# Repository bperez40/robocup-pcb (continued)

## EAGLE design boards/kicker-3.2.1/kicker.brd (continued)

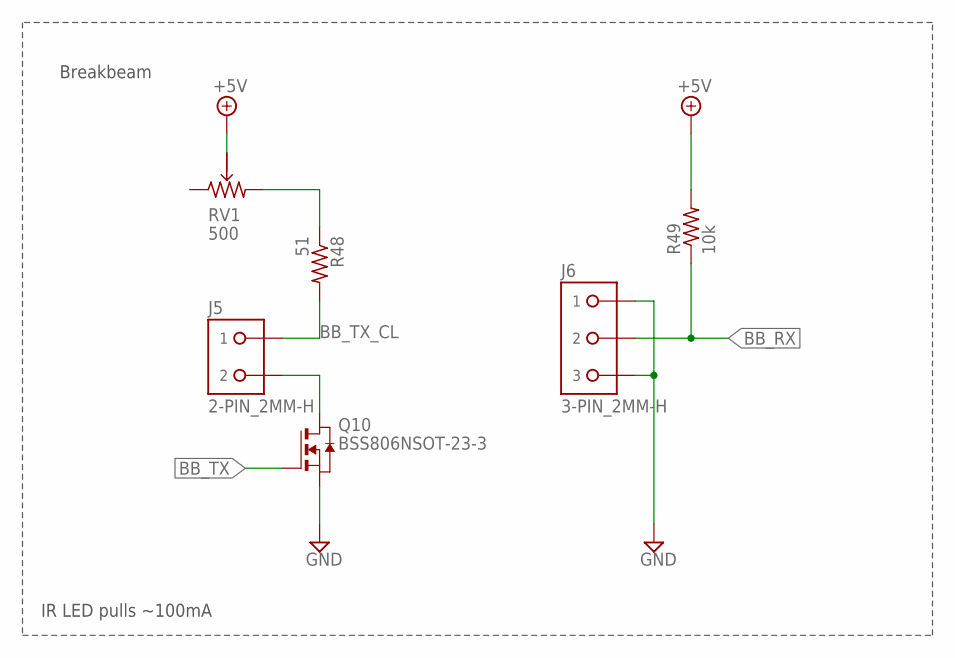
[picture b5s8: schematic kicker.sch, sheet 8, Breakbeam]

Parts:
J5: 2-PIN_2MM-H; 2MM-2-H
J6: 3-PIN_2MM-H; 2MM-3-H
Q10: BSS806NSOT-23-3; SOT95P240X110-3
R48: 51; R0603
R49: 10k; R0603
RV1: 500; PVG3G

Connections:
+5V: R49.2, RV1.P$2 (PIN2); also elsewhere on the board
BB_RX: J6.2, R49.1; also elsewhere on the board
BB_TX: Q10.1 (G); also elsewhere on the board
BB_TX_CL: J5.1, R48.2
GND: J6.1, J6.3, Q10.2 (S); also elsewhere on the board
unnamed: R48.1, RV1.P$3 (PIN3)
unnamed: J5.2, Q10.3 (D)

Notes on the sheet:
Breakbeam
IR LED pulls ~100mA

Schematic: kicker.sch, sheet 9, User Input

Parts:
J7: !BTN_KCK_PRE_EXT; 1X2
J8: !BTN_CHP_PRE_EXT; 1X2
J9: !BTN_CHG_PRE_EXT; 1X2
R50, R51, R52, R53: 10k; R0603
S1: CSS-121XB
S2, S3, S4: HDP001R

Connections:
!BTN_CHG: J9.1, R53.1, S4.C (A2); also elsewhere on the board
!BTN_CHP: J8.1, R51.1, S2.C (A2); also elsewhere on the board
!BTN_KCK: J7.1, R52.1, S3.C (A2); also elsewhere on the board
+5V: R51.2, R52.2, R53.2, S1.1 (A); also elsewhere on the board
GND: J7.2, J8.2, J9.2, S1.2 (B), S1.LEG1, S1.LEG4 (LEG2), S2.B (B1), S3.B (B1), S4.B (B1); also elsewhere on the board
MODE_SELECT: R50.2; also elsewhere on the board
unnamed: R50.1, S1.3 (COMMON)

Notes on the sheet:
Debug Mode Select
Chip/Kick Switch
Solder-in Debug Lines

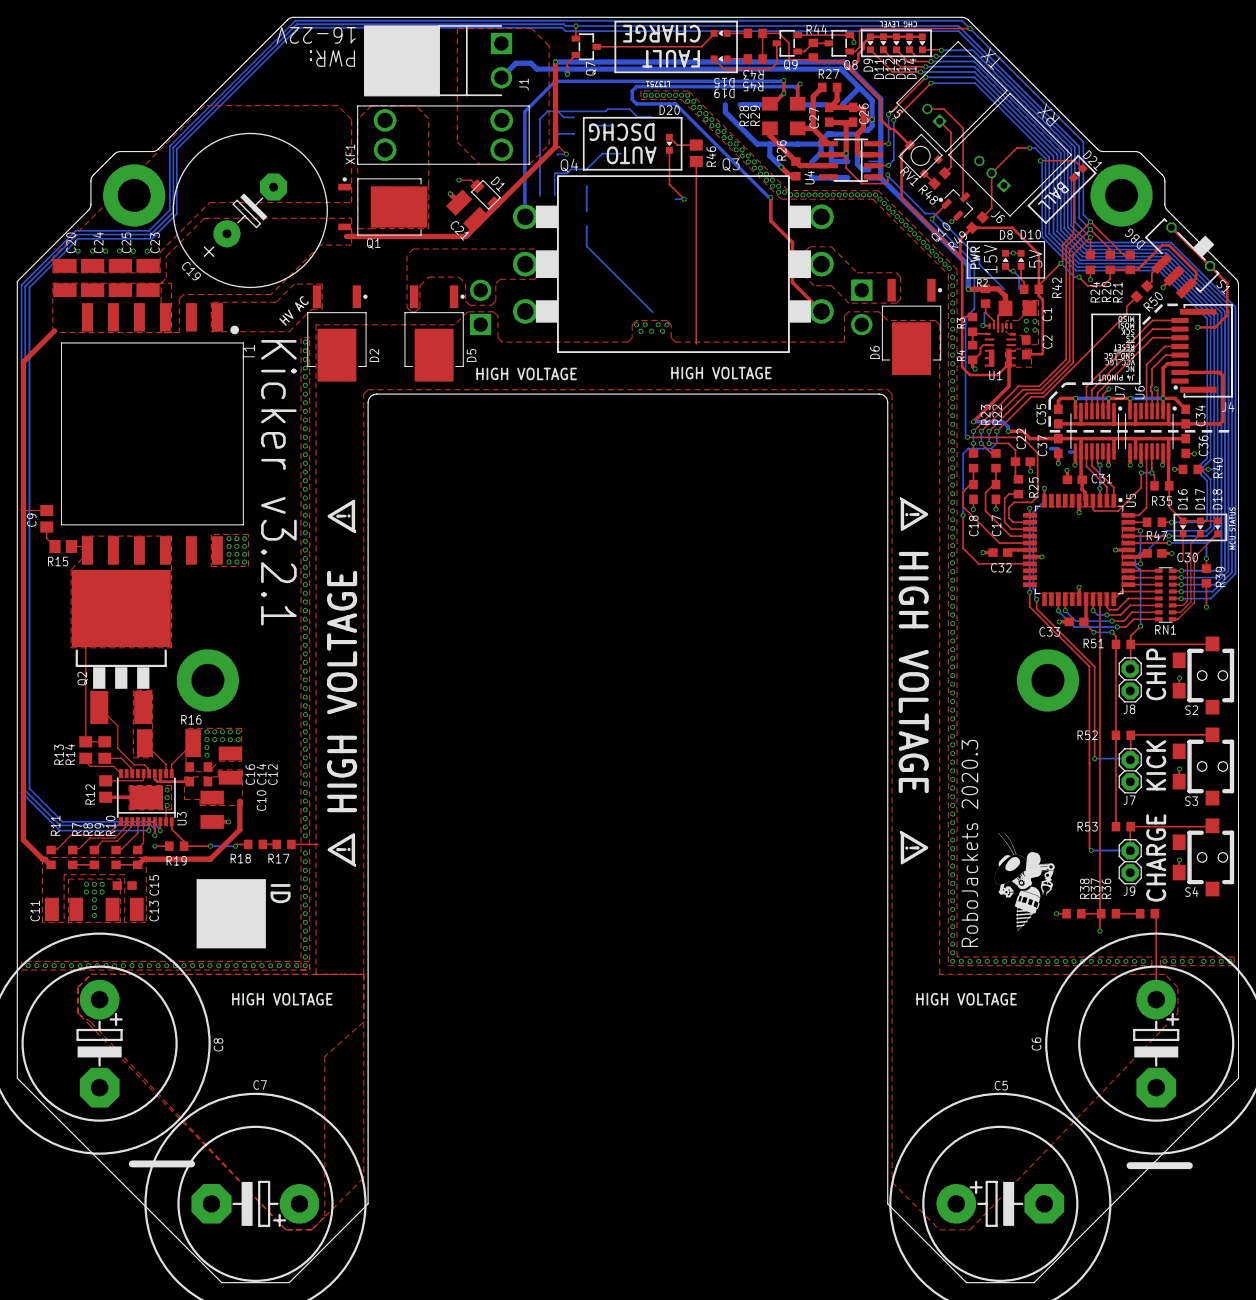
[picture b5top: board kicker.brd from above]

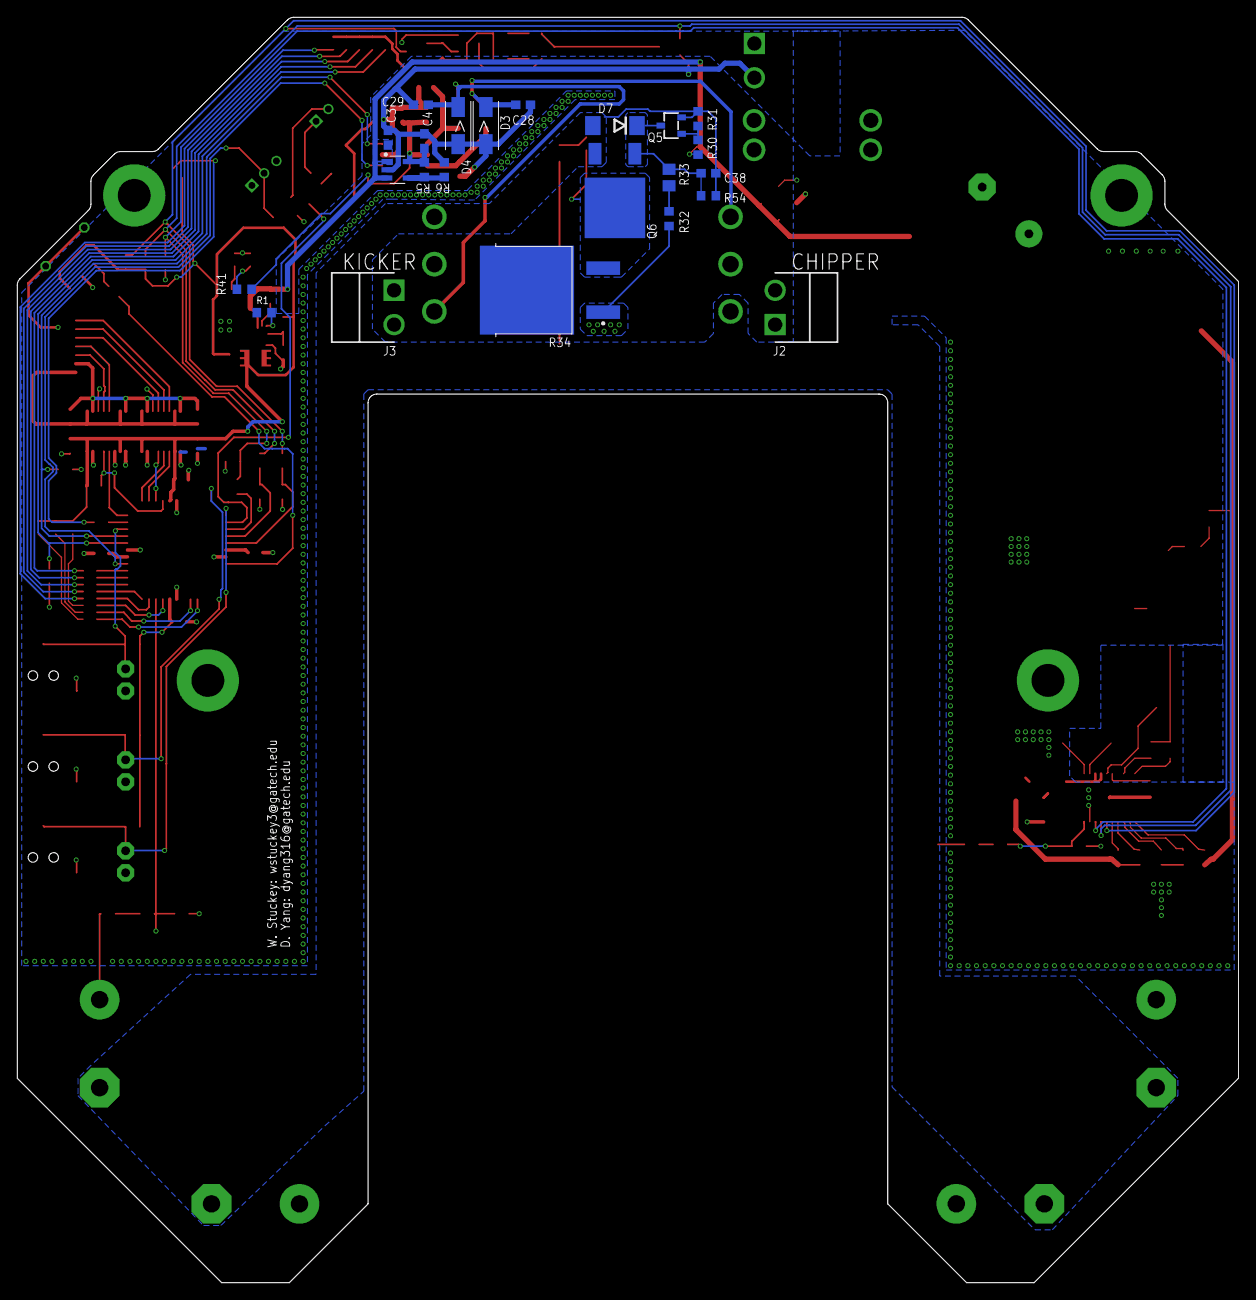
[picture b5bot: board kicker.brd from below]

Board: 2 copper layers, 141.0 x 146.1 mm, 152 parts (23 on the bottom side), 94 nets.

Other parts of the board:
U$1, U$2, U$3, U$4: WARNING2
U$5: ROBOBUZZ_0.6X

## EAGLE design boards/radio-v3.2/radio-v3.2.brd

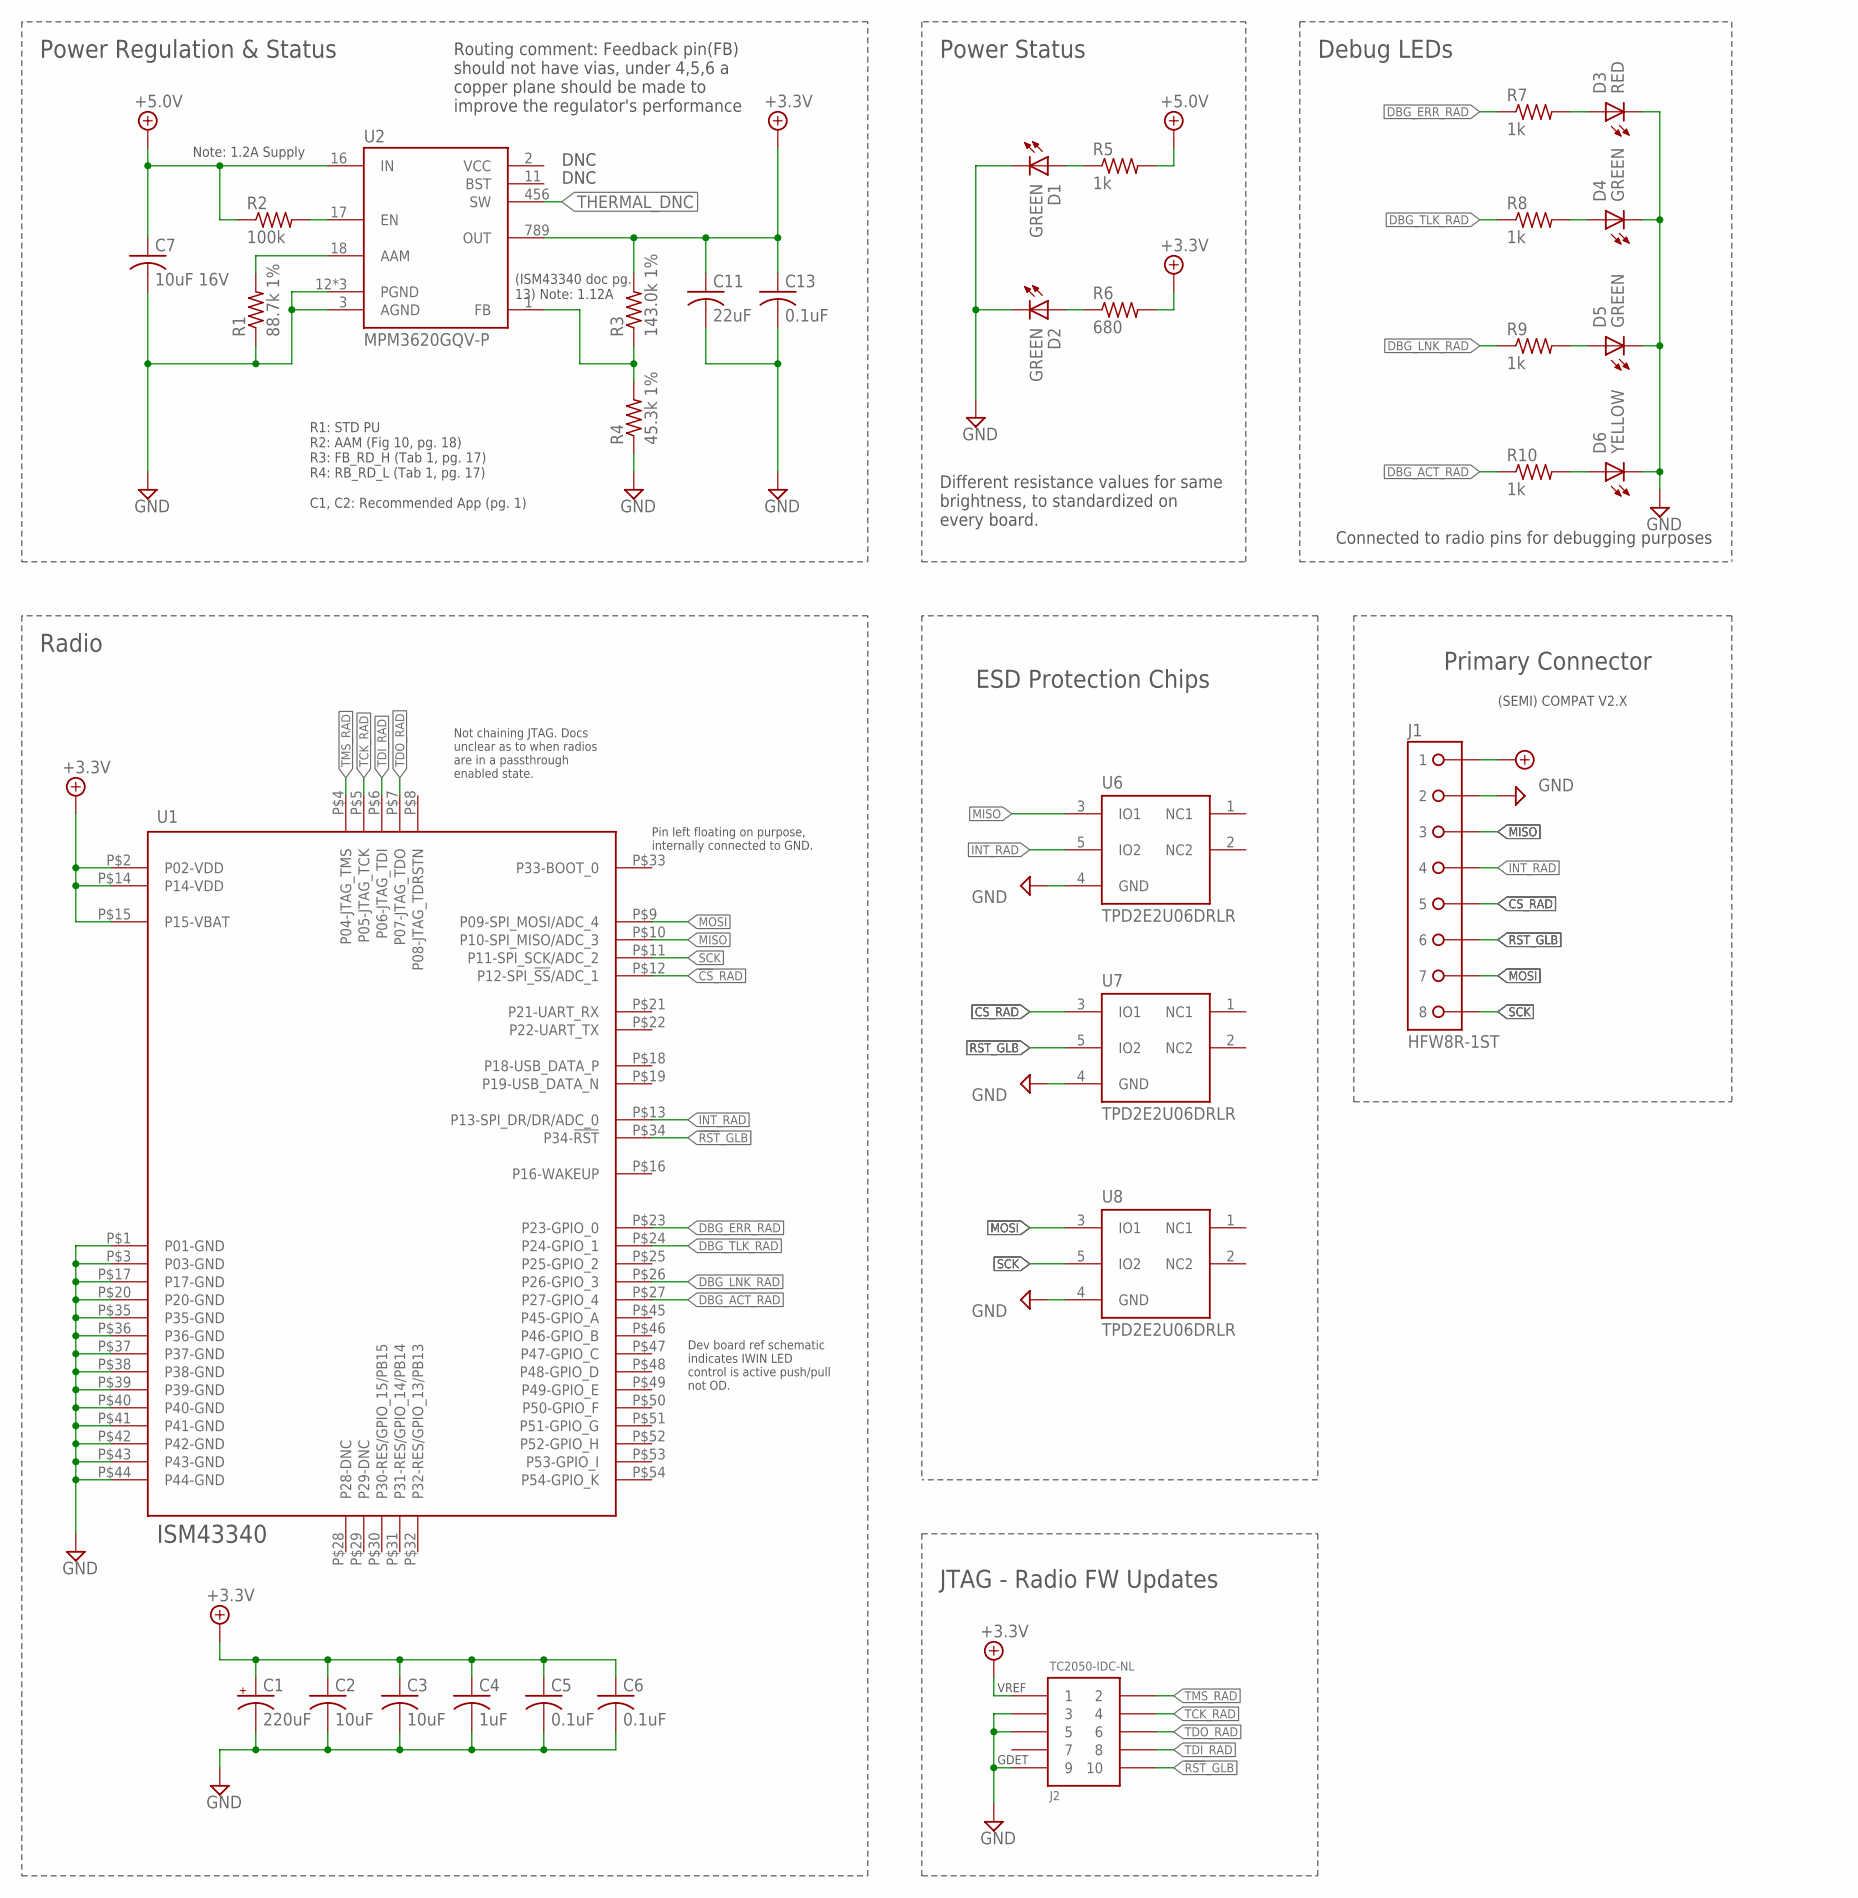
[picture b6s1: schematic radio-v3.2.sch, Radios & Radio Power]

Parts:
C1: 220uF; ECA-0JM221-HGT_HORIZ
C2, C3: 10uF; C0805
C4: 1uF; C0603
C5, C6, C13: 0.1uF; C0603
C7: 10uF 16V; C1210
C11: 22uF; C1210
D1, D2, D4, D5: GREEN; CHIP-LED0603
D3: RED; CHIP-LED0603
D6: YELLOW; CHIP-LED0603
J1: HFW8R-1ST
J2: TC2050-IDC-NL
R1: 88.7k 1%; R0603
R2: 100k; R0603
R3: 143.0k 1%; R0603
R4: 45.3k 1%; R0603
R5, R7, R8, R9, R10: 1k; R0603
R6: 680; R0603
U1: ISM43340
U2: MPM3620GQV-P
U6, U7, U8: TPD2E2U06DRLR; SOT-553

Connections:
3V3_PWR_IND: D2.A, R6.1
5V_PWR_IND: D1.A, R5.1
!CS!_RAD: J1.5, U1.P$12 (P12-SPI_!SS!/ADC_1), U7.3 (IO1)
!RST!_GLB: J1.6, J2.P$10 (10), U1.P$34 (P34-!RST!), U7.5 (IO2)
+3.3V: C1.P$1 (+), C2.1, C3.1, C4.1, C5.1, C6.1, C11.1, C13.1, J2.P$1 (1), R3.2, R6.2, U1.P$2 (P02-VDD), U1.P$14 (P14-VDD), U1.P$15 (P15-VBAT), U2.789 (OUT)
+5.0V: C7.1, J1.1, R2.1, R5.2, U2.16 (IN)
AAM: R1.2, U2.18 (AAM)
DBG_ACT_RAD: R10.1, U1.P$27 (P27-GPIO_4)
DBG_ERR: D3.A, R7.2
DBG_ERR_RAD: R7.1, U1.P$23 (P23-GPIO_0)
DBG_LNK_RAD: R9.1, U1.P$26 (P26-GPIO_3)
DBG_TLK_RAD: R8.1, U1.P$24 (P24-GPIO_1)
DGB_ACT: D6.A, R10.2
DGB_LNK: D5.A, R9.2
EN: R2.2, U2.17 (EN)
FB: R3.1, R4.2, U2.1 (FB)
GND: C1.P$2 (-), C2.2, C3.2, C4.2, C5.2, C6.2, C7.2, C11.2, C13.2, D1.C (K), D2.C (K), D3.C (K), D4.C (K), D5.C (K), D6.C (K), J1.2, J2.P$3 (3), J2.P$5 (5), J2.P$9 (9), R1.1, R4.1, U1.P$1 (P01-GND), U1.P$3 (P03-GND), U1.P$17 (P17-GND), U1.P$20 (P20-GND), U1.P$35 (P35-GND), U1.P$36 (P36-GND), U1.P$37 (P37-GND), U1.P$38 (P38-GND), U1.P$39 (P39-GND), U1.P$40 (P40-GND), U1.P$41 (P41-GND), U1.P$42 (P42-GND), U1.P$43 (P43-GND), U1.P$44 (P44-GND), U2.3 (AGND), U2.12 (PGND), U2.13 (PGND), U2.14 (PGND), U6.4 (GND), U7.4 (GND), U8.4 (GND)
INT_RAD: J1.4, U1.P$13 (P13-SPI_DR/DR/ADC_0), U6.5 (IO2)
MISO: J1.3, U1.P$10 (P10-SPI_MISO/ADC_3), U6.3 (IO1)
MOSI: J1.7, U1.P$9 (P09-SPI_MOSI/ADC_4), U8.3 (IO1)
SCK: J1.8, U1.P$11 (P11-SPI_SCK/ADC_2), U8.5 (IO2)
TCK_RAD: J2.P$4 (4), U1.P$5 (P05-JTAG_TCK)
TDI_RAD: J2.P$8 (8), U1.P$6 (P06-JTAG_TDI)
TDO_RAD: J2.P$6 (6), U1.P$7 (P07-JTAG_TDO)
THERMAL_DNC: U2.456 (SW)
TLK: D4.A, R8.2
TMS_RAD: J2.P$2 (2), U1.P$4 (P04-JTAG_TMS)

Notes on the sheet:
DNC
Primary Connector
Power Regulation & Status
Power Status
Note: 1.2A Supply
(ISM43340 doc pg. 13) Note: 1.12A
R1: STD PU R2: AAM (Fig 10, pg. 18) R3: FB_RD_H (Tab 1, pg. 17) R4: RB_RD_L (Tab 1, pg. 17) C1, C2: Recommended App (pg. 1)
Radio
Debug LEDs
VREF
GDET
JTAG - Radio FW Updates
Dev board ref schematic indicates IWIN LED control is active push/pull not OD.
Not chaining JTAG. Docs unclear as to when radios are in a passthrough enabled state.
(SEMI) COMPAT V2.X
ESD Protection Chips
Pin left floating on purpose, internally connected to GND.
Routing comment: Feedback pin(FB) should not have vias, under 4,5,6 a copper plane should be made to improve the regulator's performance
Connected to radio pins for debugging purposes
Different resistance values for same brightness, to standardized on every board.

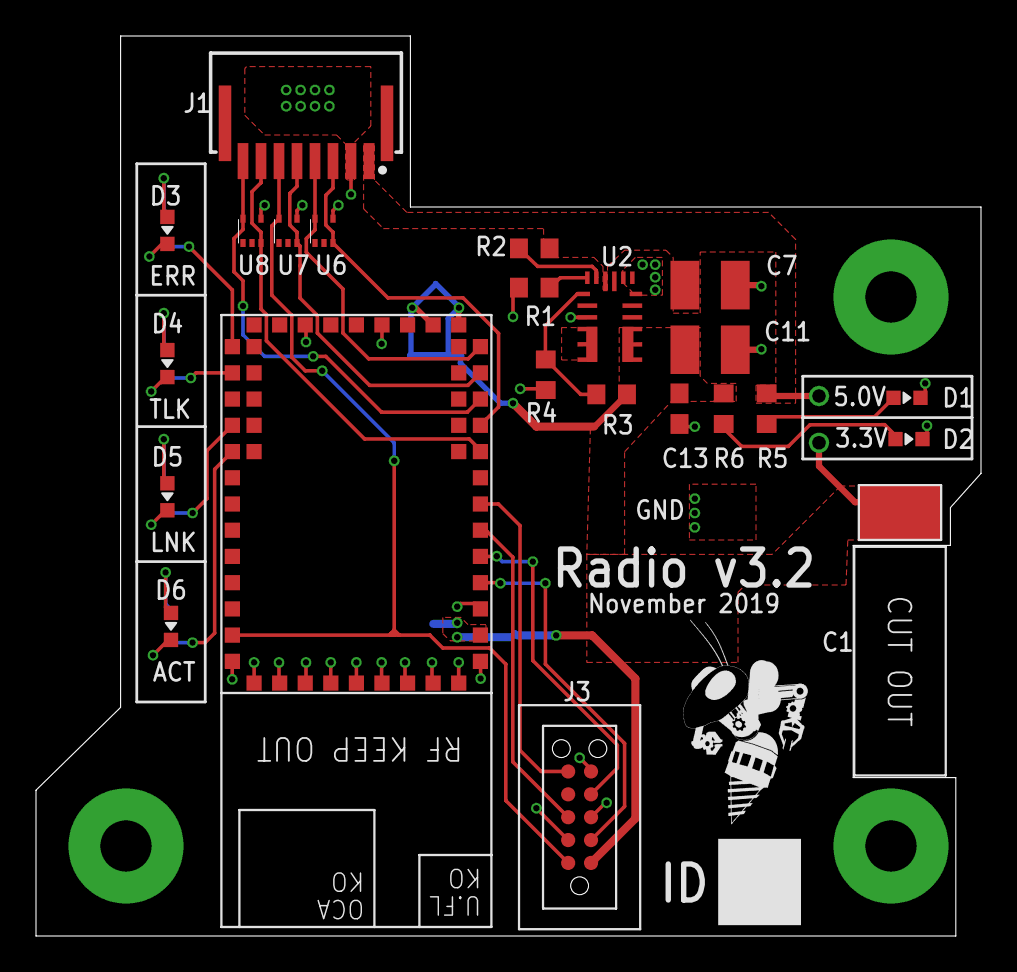
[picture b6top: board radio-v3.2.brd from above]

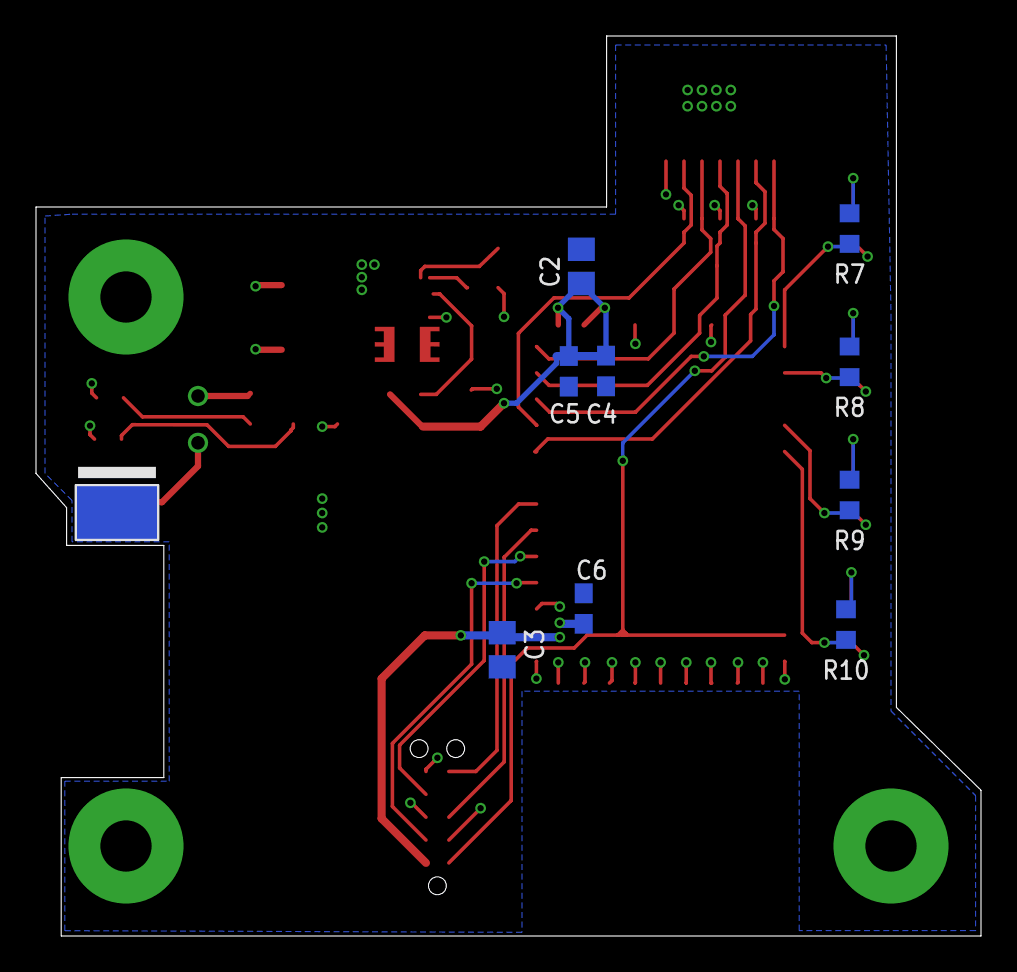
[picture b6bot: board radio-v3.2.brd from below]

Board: 2 copper layers, 52.5 x 50.0 mm, 33 parts (9 on the bottom side), 26 nets.

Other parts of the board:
U$1: ROBOBUZZ_0.6X

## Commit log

2020-02-13 Added wiring diagram
2020-03-01 radio-v4.0
2020-03-04 Radio update
2020-05-07 try for STLs
2020-05-10 control done 3d, kicker having librarie issues
2020-05-16 Added current-sense dev board
2020-05-17 kicker in progress
2020-05-18 radio done, kicker in progress
2020-05-18 kicker done, still need breakbeam and IMU
2020-05-18 IMU board in progress
2020-05-19 IMU done
2020-05-19 STLs of all boards on the robot are done
2020-05-24 Silkscreen fixes
2020-06-10 XC7A35T-1FTG256C part created in RoboJackets-IC library, creation of control-v3.5
2020-06-10 GND wired
2020-06-11 schematic progress
2020-06-12 Power FPGA done, need to add missing power sources, prog fpga in progress
2020-06-14 Schematic progress, prog almost wired, started on io banks
2020-06-20 rotated the LDO
2020-06-21 IOs for motors all linked, still need external clock, power line and battery status wiring
2020-06-23 Moved wiring diagram under doc
2020-06-23 Adjused frame
2020-06-27 removed two ground symbols from board
2020-07-02 changed supply voltage of opamps to 3V3
2020-07-08 Organized IOs, new clock missing, adding power lines
2020-07-08 cleanup
2020-07-10 fixed clearances and resized some wires from 0.5 to 0.3
2020-07-12 Updated README and removed library files
2020-07-18 added borders in board view
2020-07-23 added names to some borders
2020-07-26 FPGA board schematic ready for review!
2020-07-27 more borders
2020-07-31 replaced TLV 70450 with TLV 70433
2020-08-04 Fixed board dimensions and some other borders
2020-08-05 fixed U9 LDO connections
2020-08-09 some modif
2020-08-09 Revert "fixed U9 LDO connections"
    This reverts commit 927cff76196117dea27b8f474de1fa187c808058.
2020-08-09 fixed 3V3 connection on LDO
2020-08-10 minor formatting changes
2020-08-10 moved clock to sheet 3, removed busses in favor to individual signals
2020-08-18 last changes
2020-08-20 modifications after Arvind's review
2020-08-29 changed name of U6 border
2020-12-18 don't remember changes
2021-04-30 don't remember which changes I did as they were forever ago but I did a thing last semester
2021-06-19 TXB0102 Bi Directional Level Shifter Part
